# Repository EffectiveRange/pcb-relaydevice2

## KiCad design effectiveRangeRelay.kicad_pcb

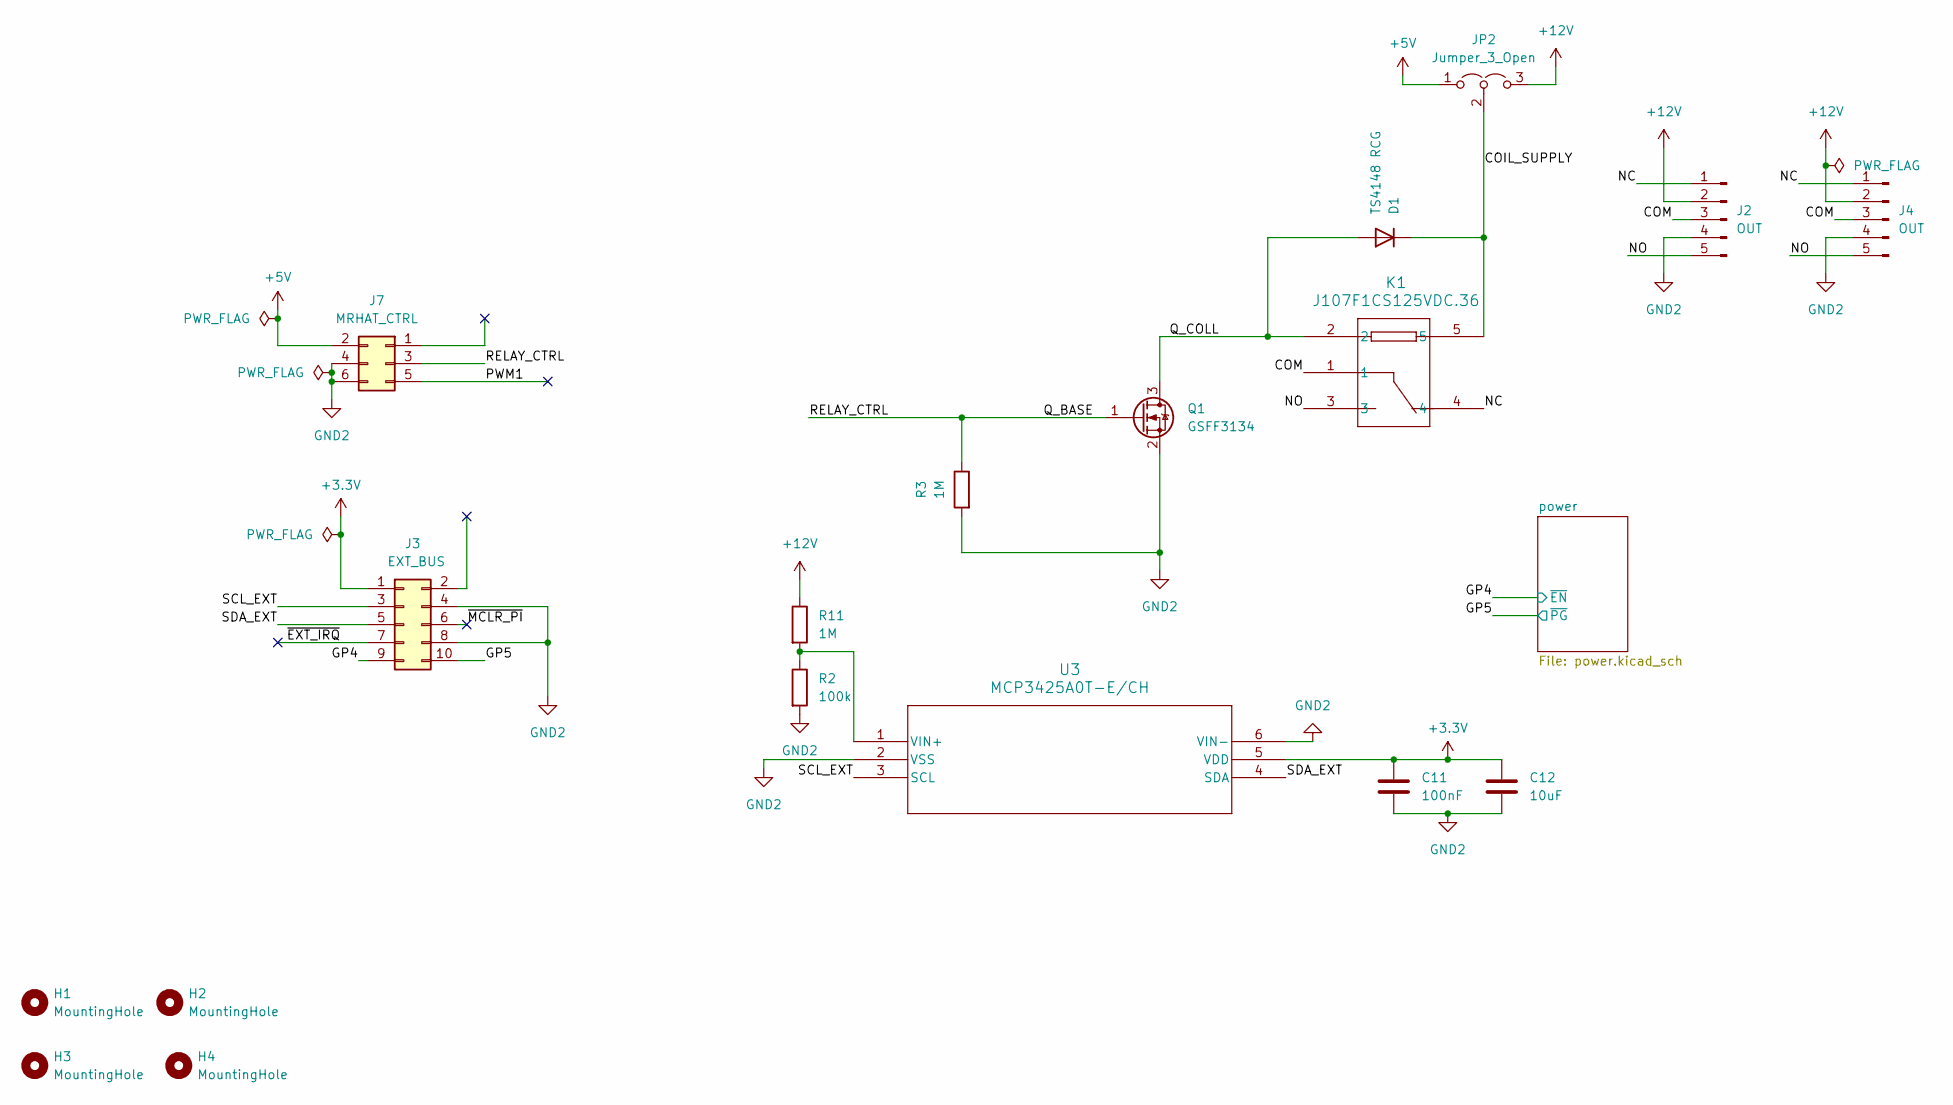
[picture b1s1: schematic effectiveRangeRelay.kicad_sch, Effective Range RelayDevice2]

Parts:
C11: 100nF; C_0402_1005Metric; MPN GRM155R71E104KE14J
C12: 10uF; C_1210_3225Metric; MPN GMC32X7R106K50N
D1: TS4148 RCG; D_0603_1608Metric; MPN TS4148 RCG
H1, H2, H3, H4: MountingHole; MountingHole_2.7mm_M2.5_DIN965
J2, J4: OUT; CONN_1935190_PXC; MPN 691137710005
J3: EXT_BUS; PinHeader_2x05_P2.54mm_Vertical; MPN 61301021121
J7: MRHAT_CTRL; PinHeader_2x03_P2.54mm_Vertical; MPN 61300621121
JP2: Jumper_3_Open; PinHeader_1x03_P2.54mm_Vertical; MPN 61300311121
K1: J107F1CS125VDC.36; RELAY5_J107F-1C_CRS; MPN J107F1CS125VDC.36
Q1: GSFF3134; SOT-723; MPN GSFF3134
R2: 100k; R_0402_1005Metric; MPN ERJ-2GEJ104X
R3: 1M; R_0402_1005Metric; MPN ERJ-2RKF1004X
R11: 1M; R_0402_1005Metric; Tolerance 1%; MPN ERJ-2RKF1004X
U3: MCP3425A0T-E/CH; SOT-23-6_MC_MCH-M; MPN MCP3425A0T-E/CH

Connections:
+3.3V: C11.1, C12.1, J3.1, U3.5 (VDD); also elsewhere on the board
+5V: J7.2, JP2.1 (A)
+12V: J2.2, J4.2, JP2.3 (B), R11.1; also elsewhere on the board
/COIL_SUPPLY: D1.1 (K), JP2.2 (C), K1.5
/COM: J2.3, J4.3, K1.1
/GP4: J3.9; also elsewhere on the board
/GP5: J3.10; also elsewhere on the board
/NC: J2.1, J4.1, K1.4
/NO: J2.5, J4.5, K1.3
/PWM1: J7.5
/Q_BASE: J7.3, Q1.1 (G), R3.1
/Q_COLL: D1.2 (A), K1.2, Q1.3 (D)
/SCL_EXT: J3.3, U3.3 (SCL)
/SDA_EXT: J3.5, U3.4 (SDA)
/~EXT_IRQ: J3.7
/~MCLR_PI: J3.6
GND2: C11.2, C12.2, J2.4, J3.4, J3.8, J4.4, J7.4, J7.6, Q1.2 (S), R2.2, R3.2, U3.2 (VSS), U3.6 (VIN-); also elsewhere on the board
unnamed: R2.1, R11.2, U3.1 (VIN+)

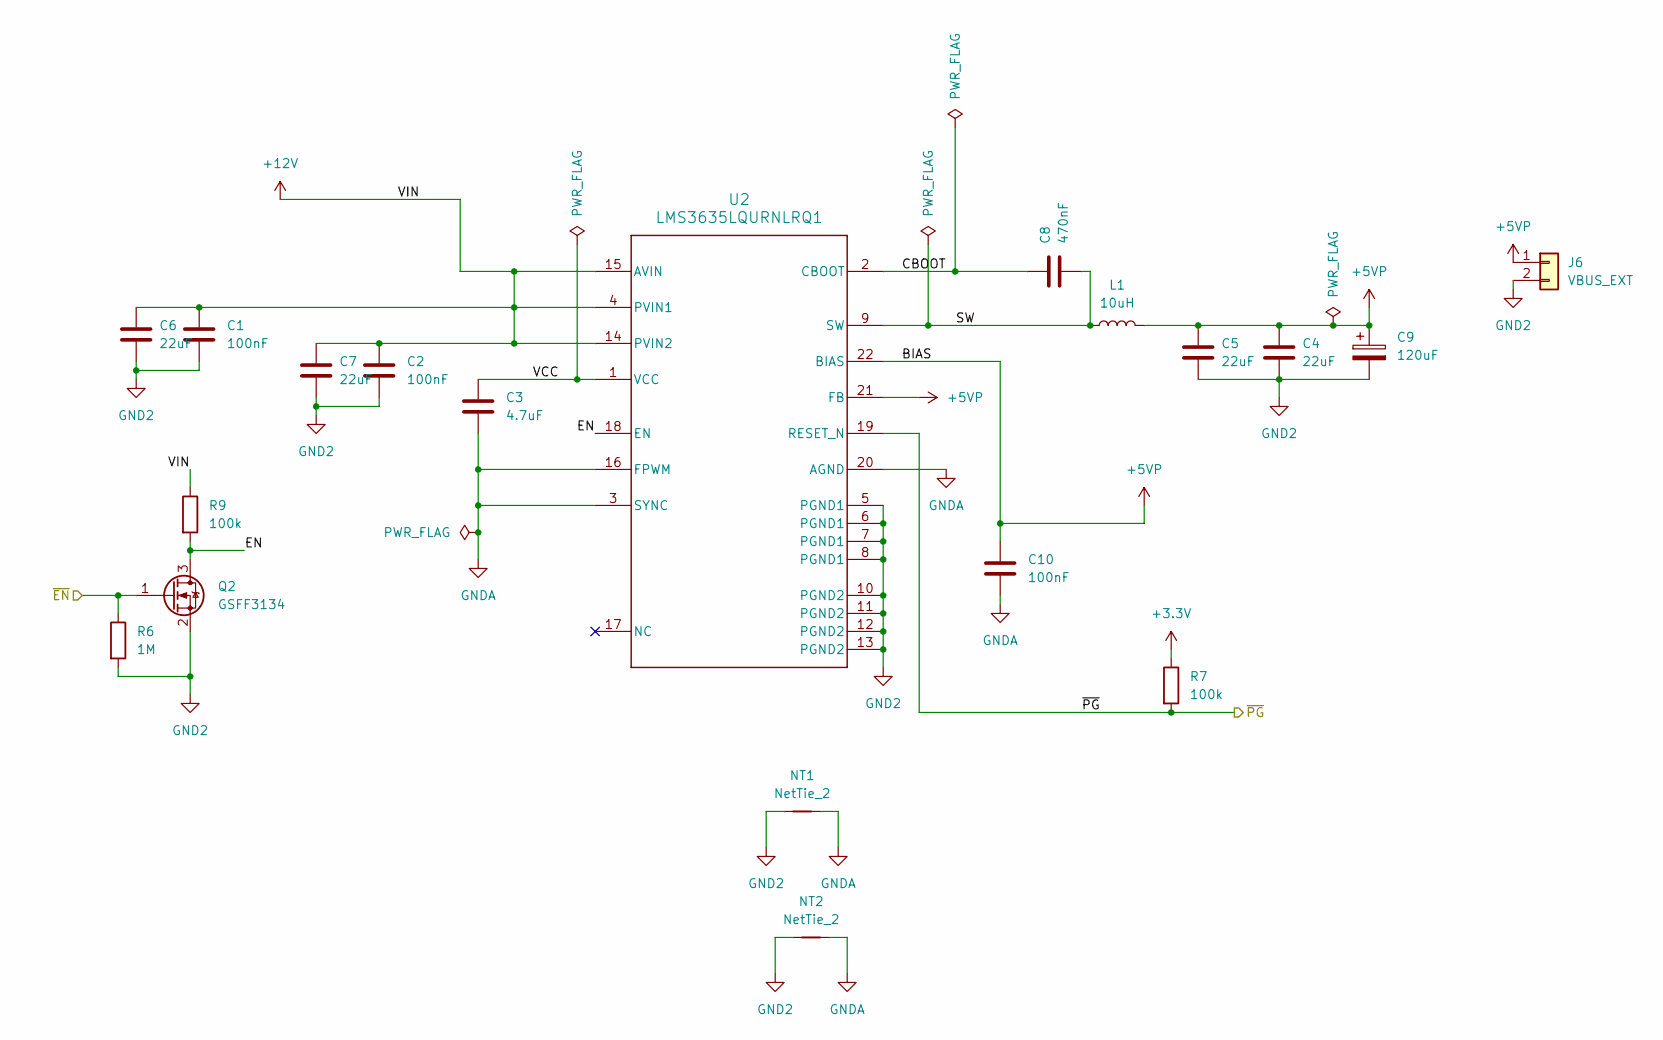
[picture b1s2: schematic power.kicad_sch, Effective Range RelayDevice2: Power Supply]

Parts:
C1, C2, C10: 100nF; C_0402_1005Metric; MPN GRM155R71E104KE14J
C3: 4.7uF; C_0603_1608Metric; MPN GRM188R6YA475KE15D
C4, C5, C6, C7: 22uF; C_0805_2012Metric; MPN GRM21BR61E226ME44K
C8: 470nF; C_0402_1005Metric; MPN GRM155R61H474ME11D
C9: 120uF; CP_Elec_6.3x5.9; MPN APXG200ARA121MF61G
J6: VBUS_EXT; CONN02_533750210_MOL; MPN 533750210
L1: 10uH; WE_7447709100; MPN 7447709100
NT1, NT2: NetTie_2; NetTie-2_SMD_Pad0.5mm
Q2: GSFF3134; SOT-723; MPN GSFF3134
R6: 1M; R_0402_1005Metric; Tolerance 1%; MPN ERJ-2RKF1004X
R7, R9: 100k; R_0402_1005Metric; MPN ERJ-2GEJ104X
U2: LMS3635LQURNLRQ1; RNL0022A_NV; MPN LMS3635LQURNLRQ1

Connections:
+3.3V: R7.1; also elsewhere on the board
+5VP: C4.1, C5.1, C9.1, C10.1, J6.1, L1.2, U2.21 (FB), U2.22 (BIAS)
+12V: C1.1, C2.1, C6.1, C7.1, R9.1, U2.4 (PVIN1), U2.14 (PVIN2), U2.15 (AVIN); also elsewhere on the board
/GP4: Q2.1 (G), R6.1; also elsewhere on the board
/GP5: R7.2, U2.19 (RESET_N); also elsewhere on the board
/power/CBOOT: C8.1, U2.2 (CBOOT)
/power/EN: Q2.3 (D), R9.2, U2.18 (EN)
/power/SW: C8.2, L1.1, U2.9 (SW)
/power/VCC: C3.1, U2.1 (VCC)
GND2: C1.2, C2.2, C4.2, C5.2, C6.2, C7.2, C9.2, J6.2, NT1.1, NT2.1, Q2.2 (S), R6.2, U2.5 (PGND1), U2.6 (PGND1), U2.7 (PGND1), U2.8 (PGND1), U2.10 (PGND2), U2.11 (PGND2), U2.12 (PGND2), U2.13 (PGND2); also elsewhere on the board
GNDA: C3.2, C10.2, NT1.2, NT2.2, U2.3 (SYNC), U2.16 (FPWM), U2.20 (AGND)

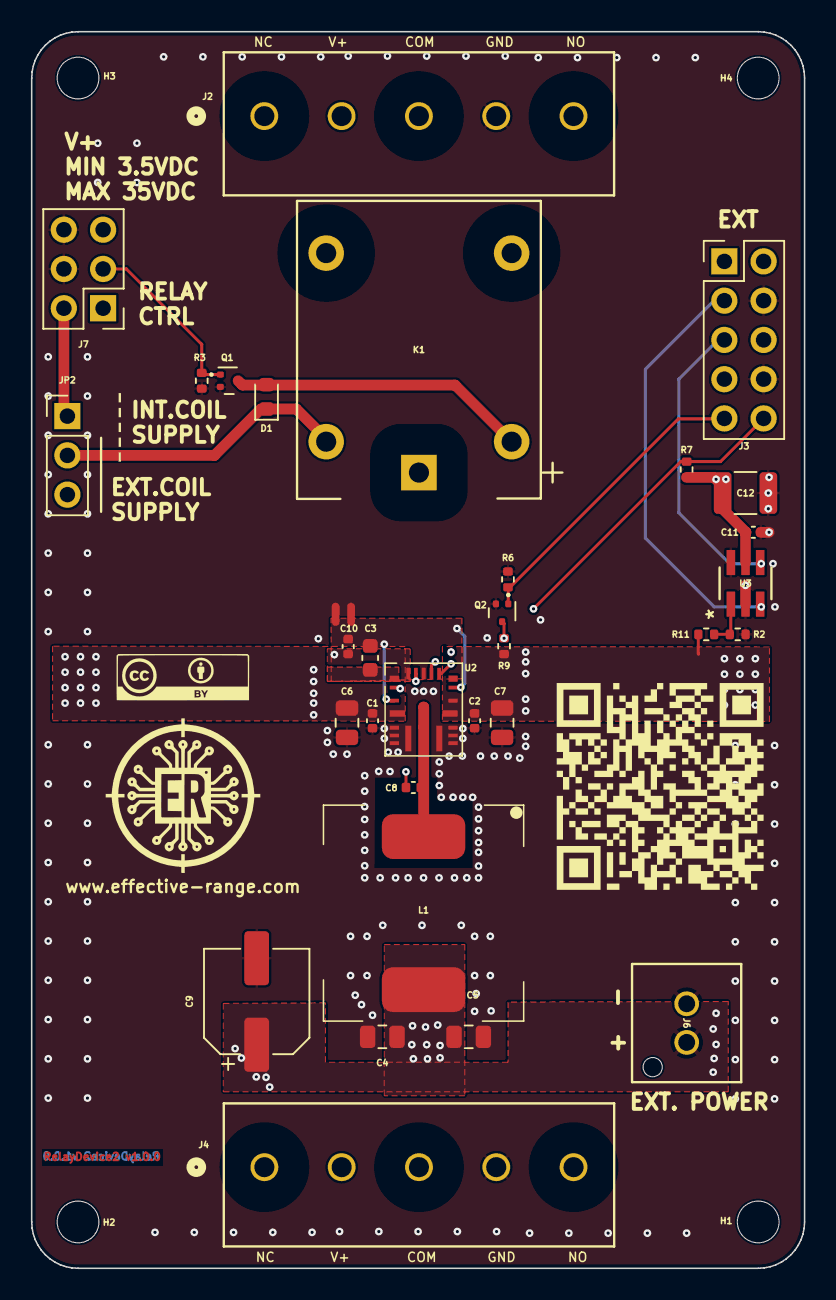
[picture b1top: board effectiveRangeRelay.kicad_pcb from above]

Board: 8 copper layers, 50.0 x 80.0 mm, 37 parts (0 on the bottom side), 21 nets.

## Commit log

2025-03-12 fix erc errors
2025-03-12 fix drc errors
2025-03-12 Bumping release from 1.0.0 to 1.0.0

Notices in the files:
effectiveRangeRelay.kicad_pcb:
visit https://creativecommons.org/licenses/by/4.0
is licensed under CC BY 4.0. To view a copy of this license,
License: MrHAT © 2024 by Ferenc Nandor Janky & Attila Gombos
